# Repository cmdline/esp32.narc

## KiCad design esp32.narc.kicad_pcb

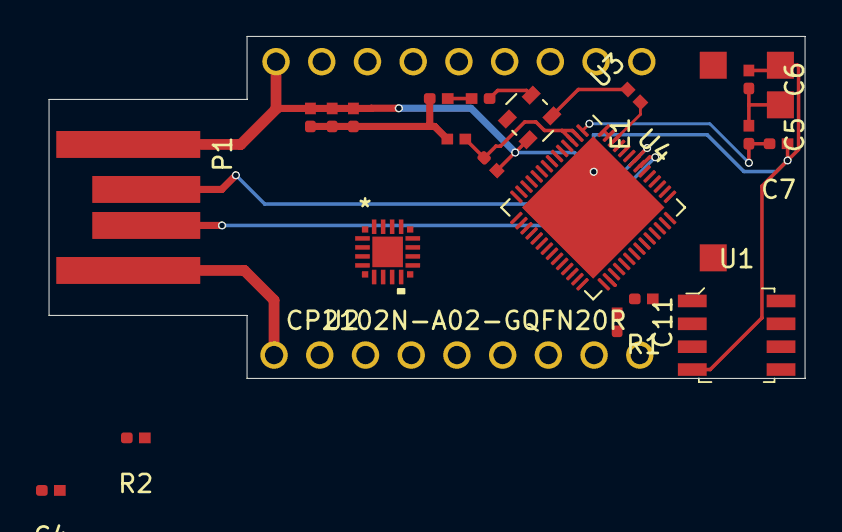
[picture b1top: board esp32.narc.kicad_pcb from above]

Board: 2 copper layers, 42.0 x 19.0 mm, 23 parts (0 on the bottom side), 20 nets.

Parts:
C0: 10uF; cap_3.20x1.60mm
C1: 1uF; cap_3.20x1.60mm
C2, C3, C11: 0.1uF; cap_3.20x1.60mm
C4, C5, C6, C7, C8: C_Small; cap_3.20x1.60mm
E1: PRO-OB-440
L0: 10nH; L_3.20x1.60mm
L1: L_Small; L_3.20x1.60mm
LE_HEADERS1: PINHEAD9
P1: usbpads
R1: 100K; cap_3.20x1.60mm
R2, R3: R_Small_US; cap_3.20x1.60mm
RE_HEADERS1: PINHEAD9
U1: W25Q32JVSSIQ_TR; SOIC-8_W5.3mm
U2: CP2102N-A02-GQFN20R
U3: 625L3C040M; 625L3C040M00000
U4: ESP32-S3; ESP32-S3-SoC

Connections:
+3V3: C0.1, C1.1, C2.1, L1.1, R3.1
+5V: LE_HEADERS1.1, P1.P1
GNDREF: C0.2, C1.2, C2.2, C6.2, C7.2, C8.2, C11.1, E1.1, P1.P4, RE_HEADERS1.1, U1.4, U3.2, U4.57
unnamed: C3.1, U3.4
unnamed: C3.2, R3.2
unnamed: C5.1, C7.1, U4.1
unnamed: C5.2, C6.1, E1.2
unnamed: C8.1, L1.2, U4.2, U4.3
unnamed: C11.2, R1.1, U1.8, U4.29
unnamed: L0.1, U3.3
unnamed: L0.2, U4.54
unnamed: P1.P2, U4.49
unnamed: P1.P3, U4.50
unnamed: R1.2, U1.1, U4.32
unnamed: U1.2, U4.34
unnamed: U1.3, U4.31
unnamed: U1.5, U4.35
unnamed: U1.6, U4.33
unnamed: U1.7, U4.30
unnamed: U4.55, U4.56

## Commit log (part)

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2021-12-27 init commit
2021-12-27 Update lib
2021-12-27 Add crystal, antenna, power per ESP32-S3 Hardware Recommendations
2021-12-27 Update esp32-sc lib
2021-12-27 init .gitignore
2021-12-27 Raw sch/board rules
2021-12-27 Update footprints
2021-12-27 Add antenna and some routes
2021-12-27 Add the pretty things!
2021-12-27 add stuff to gitignore
2021-12-27 Add local narc sch libs
2021-12-27 Add netlist
2021-12-27 added unrouted cp2102
    considering cp2104 as well
